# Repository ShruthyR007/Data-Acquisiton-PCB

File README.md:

# Data-Acquisiton-PCB
This repository contains the schematic and design files for a Data Acquisition (DAQ) system tailored for an All-Terrain Vehicle (ATV). The board is designed to interface with various sensors to monitor critical vehicle parameters, ensuring optimal performance and safety during operation.

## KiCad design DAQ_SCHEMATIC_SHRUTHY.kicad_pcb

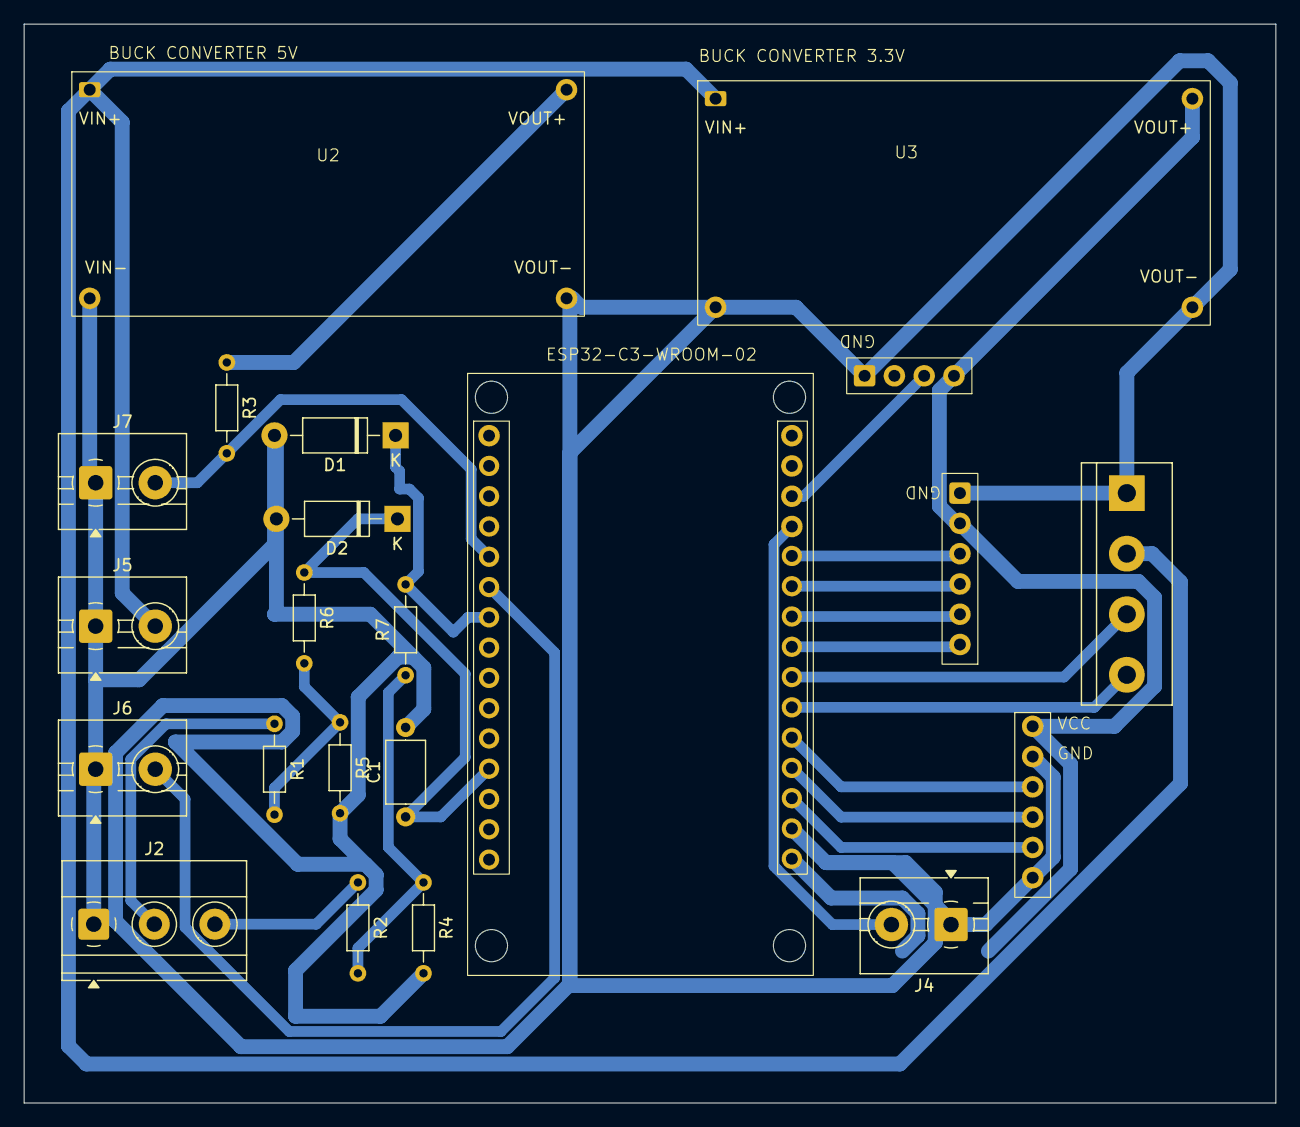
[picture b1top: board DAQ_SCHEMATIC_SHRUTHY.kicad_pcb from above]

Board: 2 copper layers, 105.0 x 90.5 mm, 23 parts (0 on the bottom side), 23 nets.

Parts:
C1: 10µF; C_Axial_L5.1mm_D3.1mm_P7.50mm_Horizontal
D1, D2: 1N47xxA; D_DO-41_SOD81_P10.16mm_Horizontal
J1: LV DATA; TerminalBlock_bornier-4_P5.08mm
J2: MOTOR RPM + BATTERY SOC; TerminalBlock_Phoenix_MKDS-1,5-3-5.08_1x03_P5.08mm_Horizont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
J3: Screw_Terminal_01x03; Wuerth_REDCUBE-THR_WP-THRBU_74650194_THR
J4, J6: DRIVE_MODE; TerminalBlock_MaiXu_MX126-5.0-02P_1x02_P5.00mm
J5: HV; TerminalBlock_MaiXu_MX126-5.0-02P_1x02_P5.00mm
J7: BATTERY TEMP; TerminalBlock_MaiXu_MX126-5.0-02P_1x02_P5.00mm
J12: SD CARD MODULE
R1, R2: 240k; R_Axial_DIN0204_L3.6mm_D1.6mm_P7.62mm_Horizontal
R3: R; R_Axial_DIN0204_L3.6mm_D1.6mm_P7.62mm_Horizontal
R4, R5: 10k; R_Axial_DIN0204_L3.6mm_D1.6mm_P7.62mm_Horizontal
R6, R7: 180; R_Axial_DIN0204_L3.6mm_D1.6mm_P7.62mm_Horizontal
U1: ESP32-C3-WROOM-02
U2: BUCK CONVERTER 5V
U3: BUCK CONVERTER 3.3V
U4: GPS UBLOX NEO-6M
U6: 10 DOF IMU MODULE

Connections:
3.3V: J12.5 (VCC), U1.30 (3V3), U3.3 (VOUT+), U4.1 (VCC), U6.1 (VCC)
5V: R3.1, U2.3 (VOUT+)
12V: J1.2, J5.2, U2.1 (VIN+), U3.1 (VIN+)
/BATTERY_TEMP: J7.2, R3.2, U1.5 (GPIO35)
/BATT_SOC: R2.2, R4.1, R7.1
/CS: J12.1 (CS), U1.23 (GPIO5)
/DRIVE_MODE: J4.2, U1.19 (RXD0)
/I2C3: U1.26 (GPIO4), U6.3 (SDA)
/I2C4: U1.27 (GPIO2), U6.4 (SCL)
/INTERRUPT: U1.28 (GPIO15), U6.5 (INT)
/MISO: J12.4 (MISO), U1.20 (GPIO21)
/MOSI: J12.3 (MOSI), U1.21 (GPIO19)
/MOTOR_RPM: R1.2, R5.1, R6.2
/MOTOR_SPEED: J6.2, U1.6 (GPIO32)
/NEXTION RX: J1.3, U1.24 (GPIO17/TX2)
/NEXTION TX: J1.4, U1.25 (GPIO/RX2)
/SCK: J12.2 (SCK), U1.22 (GPIO18)
/TX0: U1.18 (TXD0), U4.2 (RX)
GND: C1.2, D1.2 (A), D2.2 (A), J1.1, J2.1, J4.1, J5.1, J6.1, J7.1, J12.6 (GND), R4.2, R5.2, U1.29 (GND), U2.2 (VIN-), U2.4 (VOUT-), U3.2 (VIN-), U3.4 (VOUT-), U4.4 (GND), U6.2 (GND), U6.6 (FSYNC)
unnamed: D1.1 (K), R7.2, U1.7 (GPIO33)
unnamed: C1.1, D2.1 (K), R6.1, U1.12 (GPIO12)
unnamed: J2.2, R1.1
unnamed: J2.3, R2.1

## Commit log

2026-02-05 added photos of pcb schematic
